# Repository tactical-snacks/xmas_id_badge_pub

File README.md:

# xmas_id_badge
a bit of blinky xmas tree flair for an id badge or an ornament.

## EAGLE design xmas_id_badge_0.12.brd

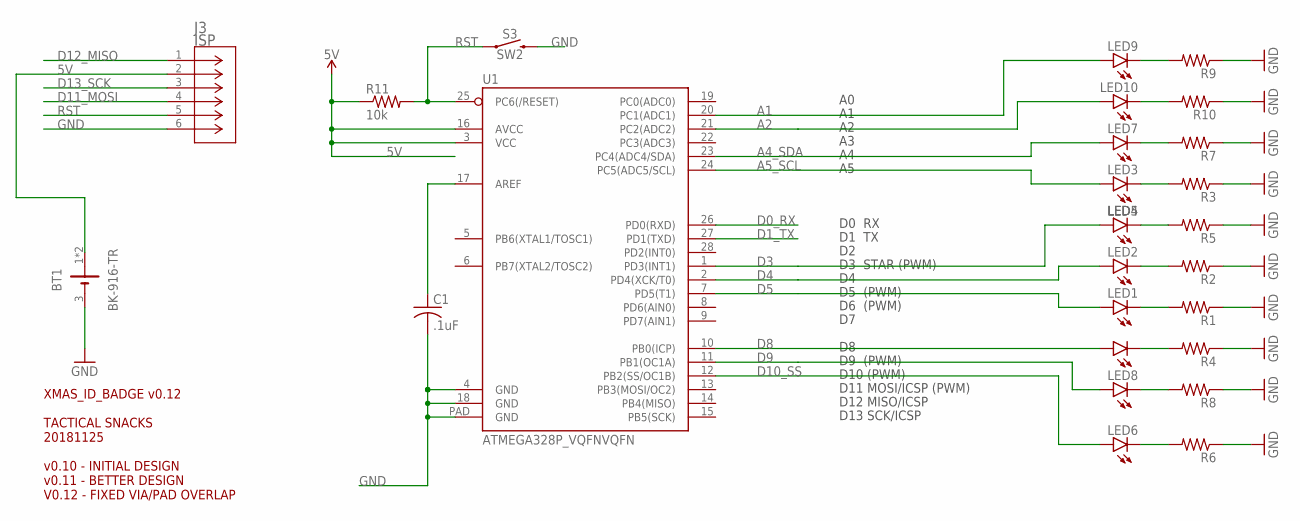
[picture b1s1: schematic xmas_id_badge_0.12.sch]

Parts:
BT1: BK-916-TR; BAT_BK-916-TR
C1: .1uF; C0603
J3: ISP; CON6_2X3_DU_FTSH-L_REV
LED1, LED2, LED3, LED4, LED5, LED6, LED7, LED8, LED9, LED10: LEDCHIP-LED0805; CHIP-LED0805
R1, R2, R3, R4, R5, R6, R7, R8, R9, R10: R-US_R0603; R0603
R11: 10k; R0805
S3: SW2; TACTILE_SWITCH_SMD_6.0X3.5MM
U1: ATMEGA328P_VQFNVQFN; VQFN-28

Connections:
5V: BT1.1 (+), BT1.2 (+), J3.2, R11.1, U1.3 (VCC), U1.16 (AVCC)
A1: LED9.A, U1.20 (PC1(ADC1))
A2: LED10.A, U1.21 (PC2(ADC2))
A4_SDA: LED7.A, U1.23 (PC4(ADC4/SDA))
A5_SCL: LED3.A, U1.24 (PC5(ADC5/SCL))
D0_RX: U1.26 (PD0(RXD))
D1_TX: U1.27 (PD1(TXD))
D3: LED5.A, U1.1 (PD3(INT1))
D4: LED2.A, U1.2 (PD4(XCK/T0))
D5: LED1.A, U1.7 (PD5(T1))
D8: LED4.A, U1.10 (PB0(ICP))
D9: LED8.A, U1.11 (PB1(OC1A))
D10_SS: LED6.A, U1.12 (PB2(SS/OC1B))
D11_MOSI: J3.4
D12_MISO: J3.1
D13_SCK: J3.3
GND: BT1.3 (-), C1.2, J3.6, R1.1, R2.1, R3.1, R4.1, R5.1, R6.1, R7.1, R8.1, R9.1, R10.1, S3.2, U1.4 (GND), U1.18 (GND), U1.PAD (GND)
unnamed: LED1.C, R1.2
unnamed: C1.1, U1.17 (AREF)
unnamed: LED2.C, R2.2
unnamed: LED3.C, R3.2
unnamed: LED4.C, R4.2
unnamed: LED6.C, R6.2
unnamed: LED5.C, R5.2
unnamed: LED7.C, R7.2
unnamed: LED8.C, R8.2
unnamed: LED9.C, R9.2
unnamed: LED10.C, R10.2
RST: J3.5, R11.2, S3.1, U1.25 (PC6(/RESET))

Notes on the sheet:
XMAS_ID_BADGE v0.12 TACTICAL SNACKS 20181125 v0.10 - INITIAL DESIGN v0.11 - BETTER DESIGN V0.12 - FIXED VIA/PAD OVERLAP
A0 A1 A2 A3 A4 A5 D0 RX D1 TX D2 D3 STAR (PWM) D4 D5 (PWM) D6 (PWM) D7 D8 D9 (PWM) D10 (PWM) D11 MOSI/ICSP (PWM) D12 MISO/ICSP D13 SCK/ICSP

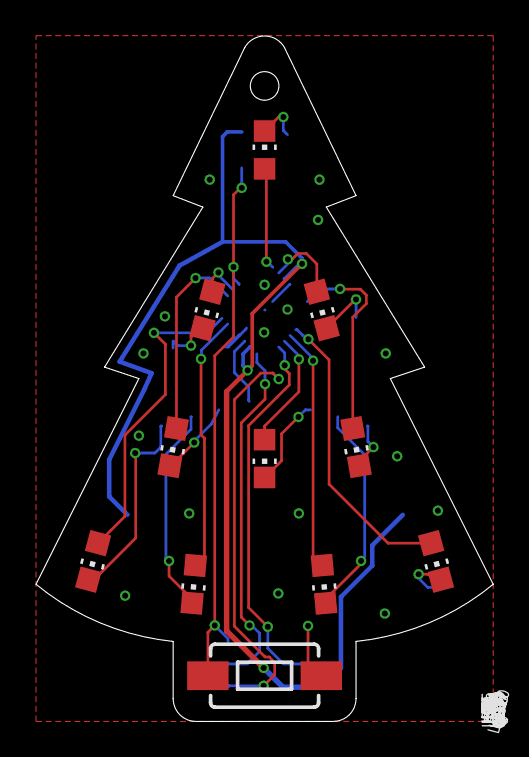
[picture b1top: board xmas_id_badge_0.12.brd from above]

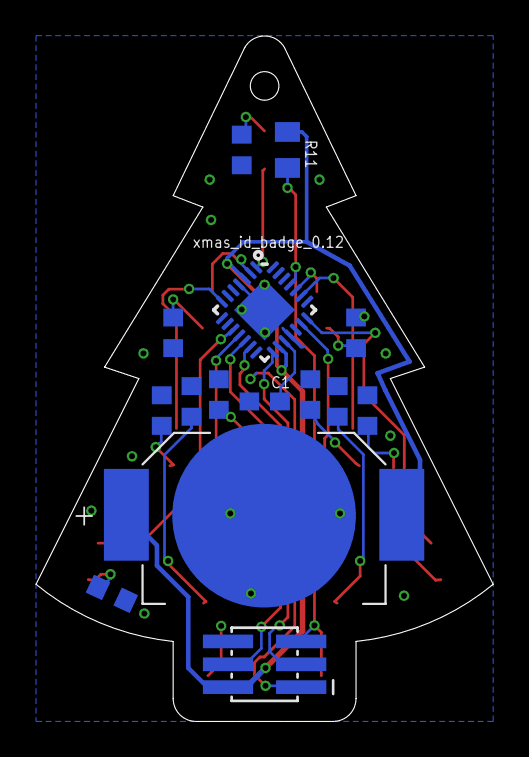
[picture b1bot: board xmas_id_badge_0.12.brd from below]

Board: 2 copper layers, 25.4 x 38.1 mm, 26 parts (15 on the bottom side), 24 nets.

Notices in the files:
parts and their libraries:
SparkFun-IC-Microcontroller: Licensing: Creative Commons ShareAlike 4.0 International - https://creativecommons.org/licenses/by-sa/4.0
